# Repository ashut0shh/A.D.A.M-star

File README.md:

# A.D.A.M-star
a test for alziemer's and dementia using praxia

1.download the arduino ide

2.upload arduino isp's code from examples->arduinoisp

3.make the pinout as shown in the pinout file

4.burn bootloader (if you upload any new code to uno i.e. not attiny then run isp again) 

5.run the test codes to make sure the individual components are working properly

6.run the final code 

7.locate avrdude in your arduino folder

8.to obtain eeprom data run the following below identify the file and open it

9.avrdude -C /path/to/avrdude.conf -v -p attiny85 -c stk500v1 -P /dev/ttyUSB0 -b 19200 -U eeprom:r:backup_eeprom.hex:i

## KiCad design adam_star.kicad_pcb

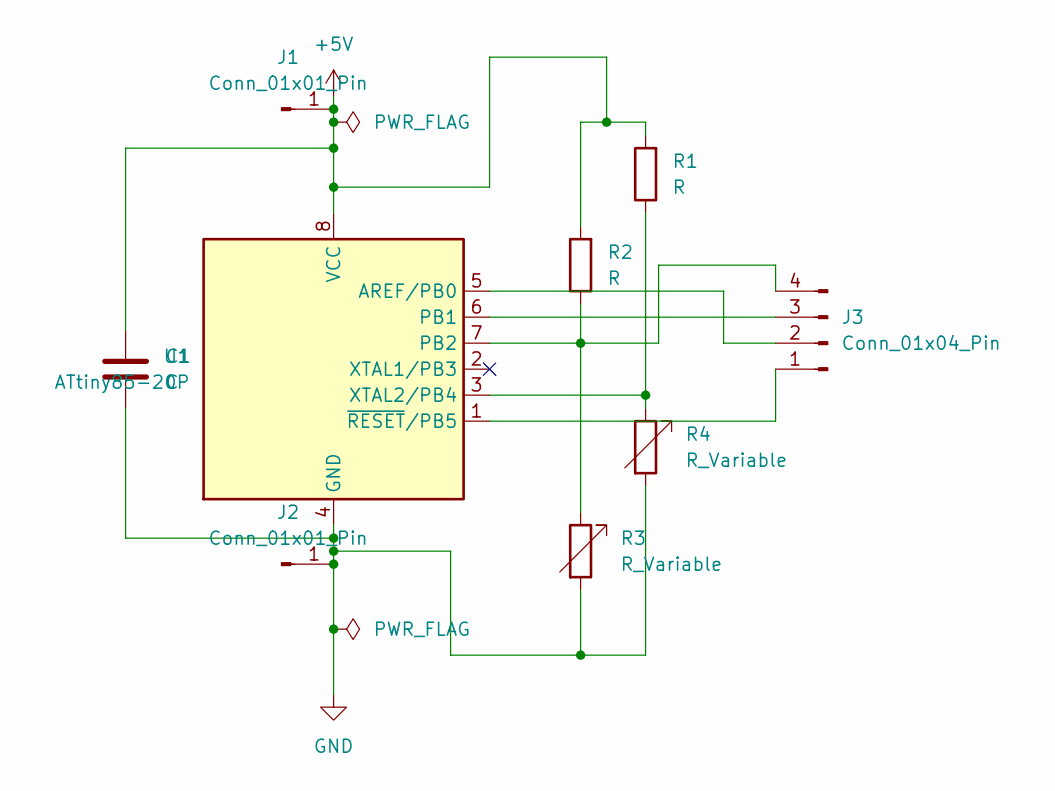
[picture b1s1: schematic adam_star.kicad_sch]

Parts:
C1: C; C_Disc_D3.0mm_W2.0mm_P2.50mm
J1: Conn_01x01_Pin; Pin_D0.7mm_L6.5mm_W1.8mm_FlatFork
J2: Conn_01x01_Pin; Pin_D1.0mm_L10.0mm
J3: Conn_01x04_Pin; PinHeader_1x04_P1.27mm_Vertical
R1, R2: R; R_Axial_DIN0207_L6.3mm_D2.5mm_P5.08mm_Vertical
R3, R4: R_Variable; R_Axial_DIN0204_L3.6mm_D1.6mm_P1.90mm_Vertical
U1: ATtiny85-20P; DIP-8_W7.62mm

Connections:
+5V: C1.1, J1.1, R1.2, R2.2, U1.8 (VCC)
GND: C1.2, J2.1, R3.2, R4.2, U1.4 (GND)
unnamed: J3.1, U1.1 (~RESET/PB5)
unnamed: J3.2, U1.5 (AREF/PB0)
unnamed: J3.3, U1.6 (PB1)
unnamed: J3.4, R2.1, R3.1, U1.7 (PB2)
unnamed: R1.1, R4.1, U1.3 (XTAL2/PB4)

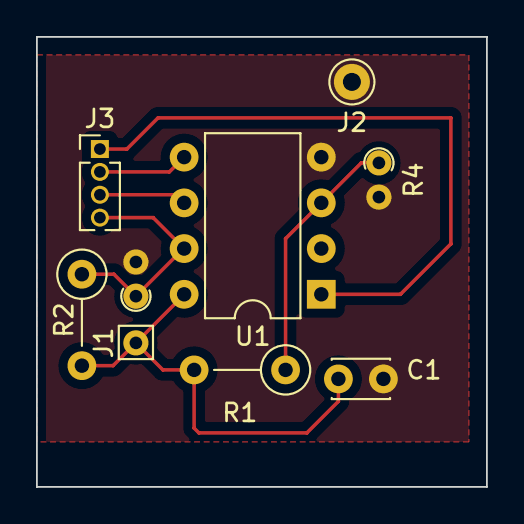
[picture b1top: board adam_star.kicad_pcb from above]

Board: 2 copper layers, 25.0 x 25.0 mm, 9 parts (0 on the bottom side), 7 nets.

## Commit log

2025-08-09 Create bootloader
2025-08-09 Create fsr test code on arduino
2025-08-09 Create attiny eeprom
2025-08-09 Create eeprom_test_file
2025-08-10 Create 1_analog_eeprom_test_code
2025-08-10 Create eeprom_test_code_2fsr's
2025-08-10 Create classifier_with_fsr
2025-08-10 Create sample correct output
2025-08-10 Create pinout connections
2025-08-10 Rename classifier_with_fsr to classifier_with_fsr_final
2025-08-10 Create BOM
2025-08-10 Create problemstatement
2025-08-14 Rename image.png to schematic.png
